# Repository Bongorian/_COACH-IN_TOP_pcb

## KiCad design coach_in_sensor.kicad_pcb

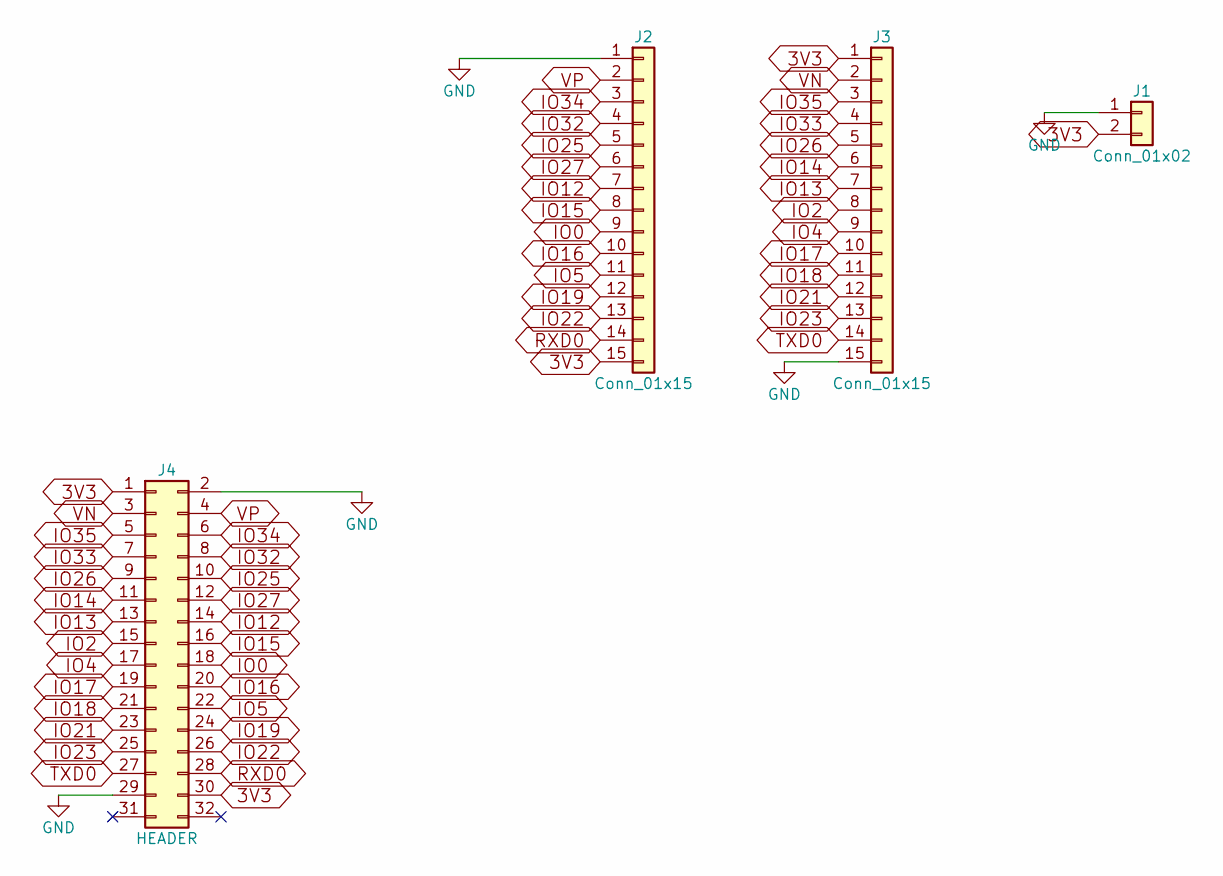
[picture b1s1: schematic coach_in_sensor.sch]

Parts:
J1: Conn_01x02; Pin_Header_Straight_1x02_Pitch2.54mm
J2, J3: Conn_01x15; Pin_Header_Straight_1x15_Pitch2.54mm
J4: HEADER; DF1230DS05V48

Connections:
3V3: J1.2, J2.15, J3.1, J4.1, J4.30
GND: J1.1, J2.1, J3.15, J4.2, J4.29
IO0: J2.9, J4.18
IO2: J3.8, J4.15
IO4: J3.9, J4.17
IO5: J2.11, J4.22
IO12: J2.7, J4.14
IO13: J3.7, J4.13
IO14: J3.6, J4.11
IO15: J2.8, J4.16
IO16: J2.10, J4.20
IO17: J3.10, J4.19
IO18: J3.11, J4.21
IO19: J2.12, J4.24
IO21: J3.12, J4.23
IO22: J2.13, J4.26
IO23: J3.13, J4.25
IO25: J2.5, J4.10
IO26: J3.5, J4.9
IO27: J2.6, J4.12
IO32: J2.4, J4.8
IO33: J3.4, J4.7
IO34: J2.3, J4.6
IO35: J3.3, J4.5
RXD0: J2.14, J4.28
TXD0: J3.14, J4.27
VN: J3.2, J4.3
VP: J2.2, J4.4

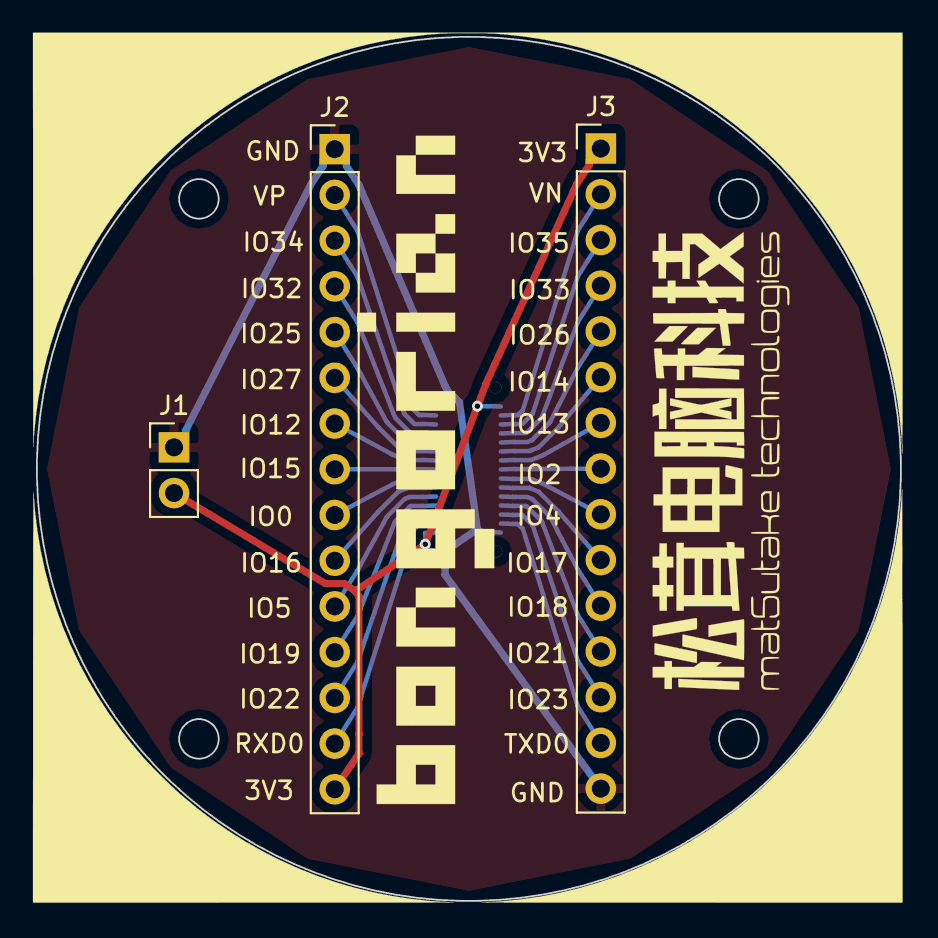
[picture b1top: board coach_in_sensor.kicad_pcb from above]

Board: 2 copper layers, 48.0 x 48.0 mm, 4 parts (1 on the bottom side), 28 nets.

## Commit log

2018-06-26 init
